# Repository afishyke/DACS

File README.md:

# DACS: Digital Automatic Changeover Switch

DACS is a discrete-logic power changeover controller that monitors grid health and switches loads between mains and inverter/battery supply. It is designed to avoid relay chatter by requiring sustained bad/good conditions before switching.

The full finite state machine (FSM), Boolean equations, and timing behavior are documented in `FSM/README.md`.

## What this project is

- A hardware-first automatic changeover system (no microcontroller in the switching core).
- A three-block architecture: sensing and conditioning, FSM decision logic, and relay output stage.
- A validated FSM implementation in both Logisim and Verilog.
- A delay-justification analysis pipeline for power-quality disturbance datasets.

## Visual overview

### 1) Full hardware architecture (KiCad)

### 2) GRID_OK comparator generation (LTspice)

### 3) Power-quality context plot

### 4) Disturbance class signal examples (delay analysis)

## Repository map

- `hardware/kicad/`: complete KiCad design (`.kicad_sch`, `.kicad_pcb`, exports).
- `grid_ok_generation/`: LTspice comparator model and generated diagram for `GRID_OK` logic.
- `simulations/logisim/`: Logisim-evolution FSM implementation.
- `simulations/verilog/`: synthesizable FSM RTL (`FSM_Grid_Stability_v2.v`).
- `simulations/ltspice/`: LTspice analog simulation files.
- `FSM/`: equation-level FSM documentation.
- `problem_statement/`: source image/script + data citation used in early framing.
- `delay_justification/`: EDA script outputs, plots, and reports for timing-delay defensibility.

## How DACS works (end-to-end)

1. **Input conditioning (Block 1):** rectifies and scales AC sense, checks voltage window and frequency window, and verifies battery level.
2. **Grid health flag generation:** combines voltage + frequency validity into a digital `GRID_OK` signal.
3. **FSM logic (Block 2):** samples `GRID_OK` on `FSM_CLK`, uses state memory + counters to enforce delay windows.
4. **Output drive (Block 3):** relay drivers route power source and shed non-essential load during backup operation.

## Core timing and threshold numbers

- FSM clock is approximately 5 Hz (report uses 5 Hz for verification, i.e. 200 ms/cycle).
- Fault confirmation window: 3 cycles (`~600 ms` at 5 Hz).
- Recovery confirmation window: 5 cycles (`~1.0 s` at 5 Hz).
- Voltage monitor window used in the design documentation is approximately:
  - upper threshold: `~4.08 V`
  - lower threshold: `~2.78 V`

Clock equation used in design notes:

$$
f = \frac{1.44}{(R_a + 2R_b)C}
$$

With `R_a = 1k\Omega`, `R_b = 150k\Omega`, `C = 1\mu F`:

$$
f \approx 4.8\,\text{Hz}, \quad T = \frac{1}{f} \approx 0.21\,\text{s}
$$

## FSM states (high level)

| State | Bits | Meaning |
| --- | --- | --- |
| ST00 | `00` | Grid mode (normal operation) |
| ST01 | `01` | Grid fault detected, waiting for confirmation |
| ST10 | `10` | Backup mode (grid confirmed bad) |
| ST11 | `11` | Grid returned, waiting for stability confirmation |

Transition intent:

- `ST00 -> ST01`: grid falls.
- `ST01 -> ST10`: fault persists until fault timer expires.
- `ST10 -> ST11`: grid returns.
- `ST11 -> ST00`: grid remains healthy until stability timer done.
- Fast rollback paths protect against short disturbances (`ST01 -> ST00`, `ST11 -> ST10`).

For the complete Boolean equations (`GRID_FALL`, `TIMER_05`, `STABILITY_DONE`, `D0`, `D1`, all term-level equations), see `FSM/README.md`.

## Verification artifacts

From the FSM verification campaign artifacts in this repository:

- 2779 automated checks reported, 0 mismatches.
- State occupancy observed:
  - ST00: 169 cycles (42.5%)
  - ST01: 96 cycles (24.1%)
  - ST10: 79 cycles (19.9%)
  - ST11: 54 cycles (13.6%)

Detailed state equations and transition logic are documented in `FSM/README.md`.

## Delay-justification EDA (dataset side)

The `delay_justification/` folder contains a full analysis pipeline for disturbance classes (17 classes, one-cycle signals at 5 kHz sampling). It supports the claim that non-zero observation windows are required before robust disturbance discrimination.

Useful plots include:

- `delay_justification/eda_outputs/plots/representative_signals_per_class.png`
- `delay_justification/eda_outputs/plots/overlay_transient_related_classes.png`
- `delay_justification/eda_outputs/plots/scatter_transient_vs_sagswell_derivative_vs_spectralspread.png`

## Main source files

- Verilog FSM: `simulations/verilog/FSM_Grid_Stability_v2.v`
- Logisim FSM: `simulations/logisim/FSM_Grid_Stabilityiteration_FINAL112233.XML (1).circ`
- Comparator LTspice: `grid_ok_generation/comparator_grid_ok.asc`
- Hardware schematic source: `hardware/kicad/schematic.kicad_sch`

## References and citations

- FSM implementation references: `simulations/verilog/FSM_Grid_Stability_v2.v`, `simulations/logisim/FSM_Grid_Stabilityiteration_FINAL112233.XML (1).circ`
- Smart-meter citation used in problem framing: `problem_statement/citations.txt`
- Comparator SPICE model source note: `grid_ok_generation/resources.txt`

## License

MIT. See `LICENSE`.

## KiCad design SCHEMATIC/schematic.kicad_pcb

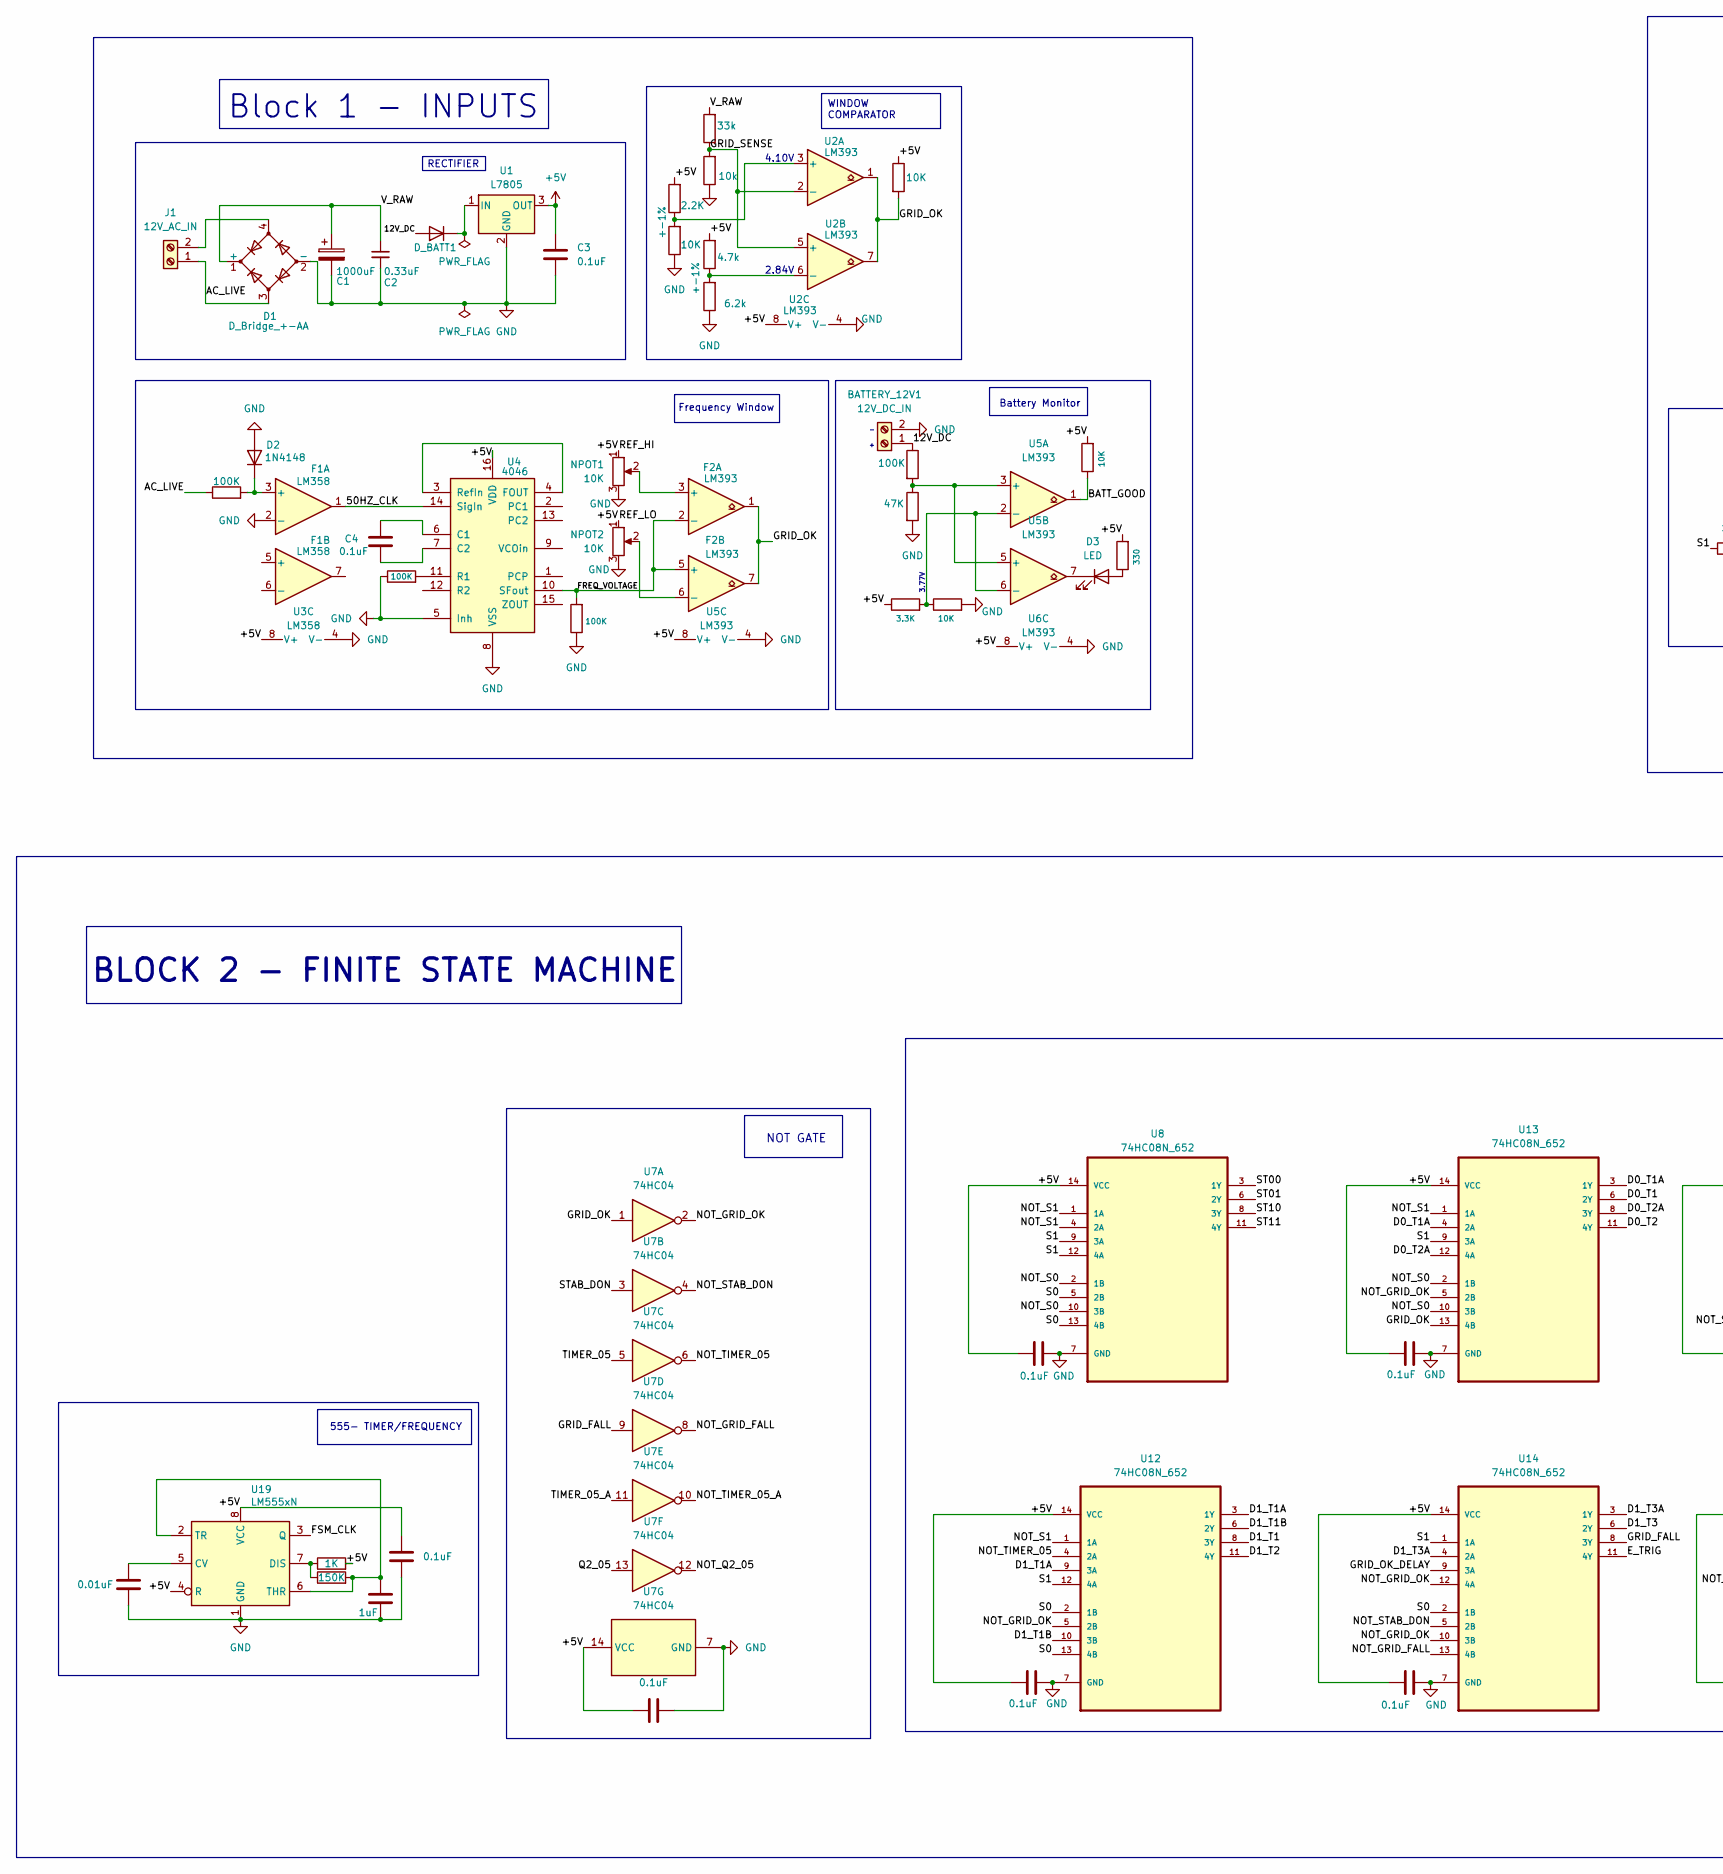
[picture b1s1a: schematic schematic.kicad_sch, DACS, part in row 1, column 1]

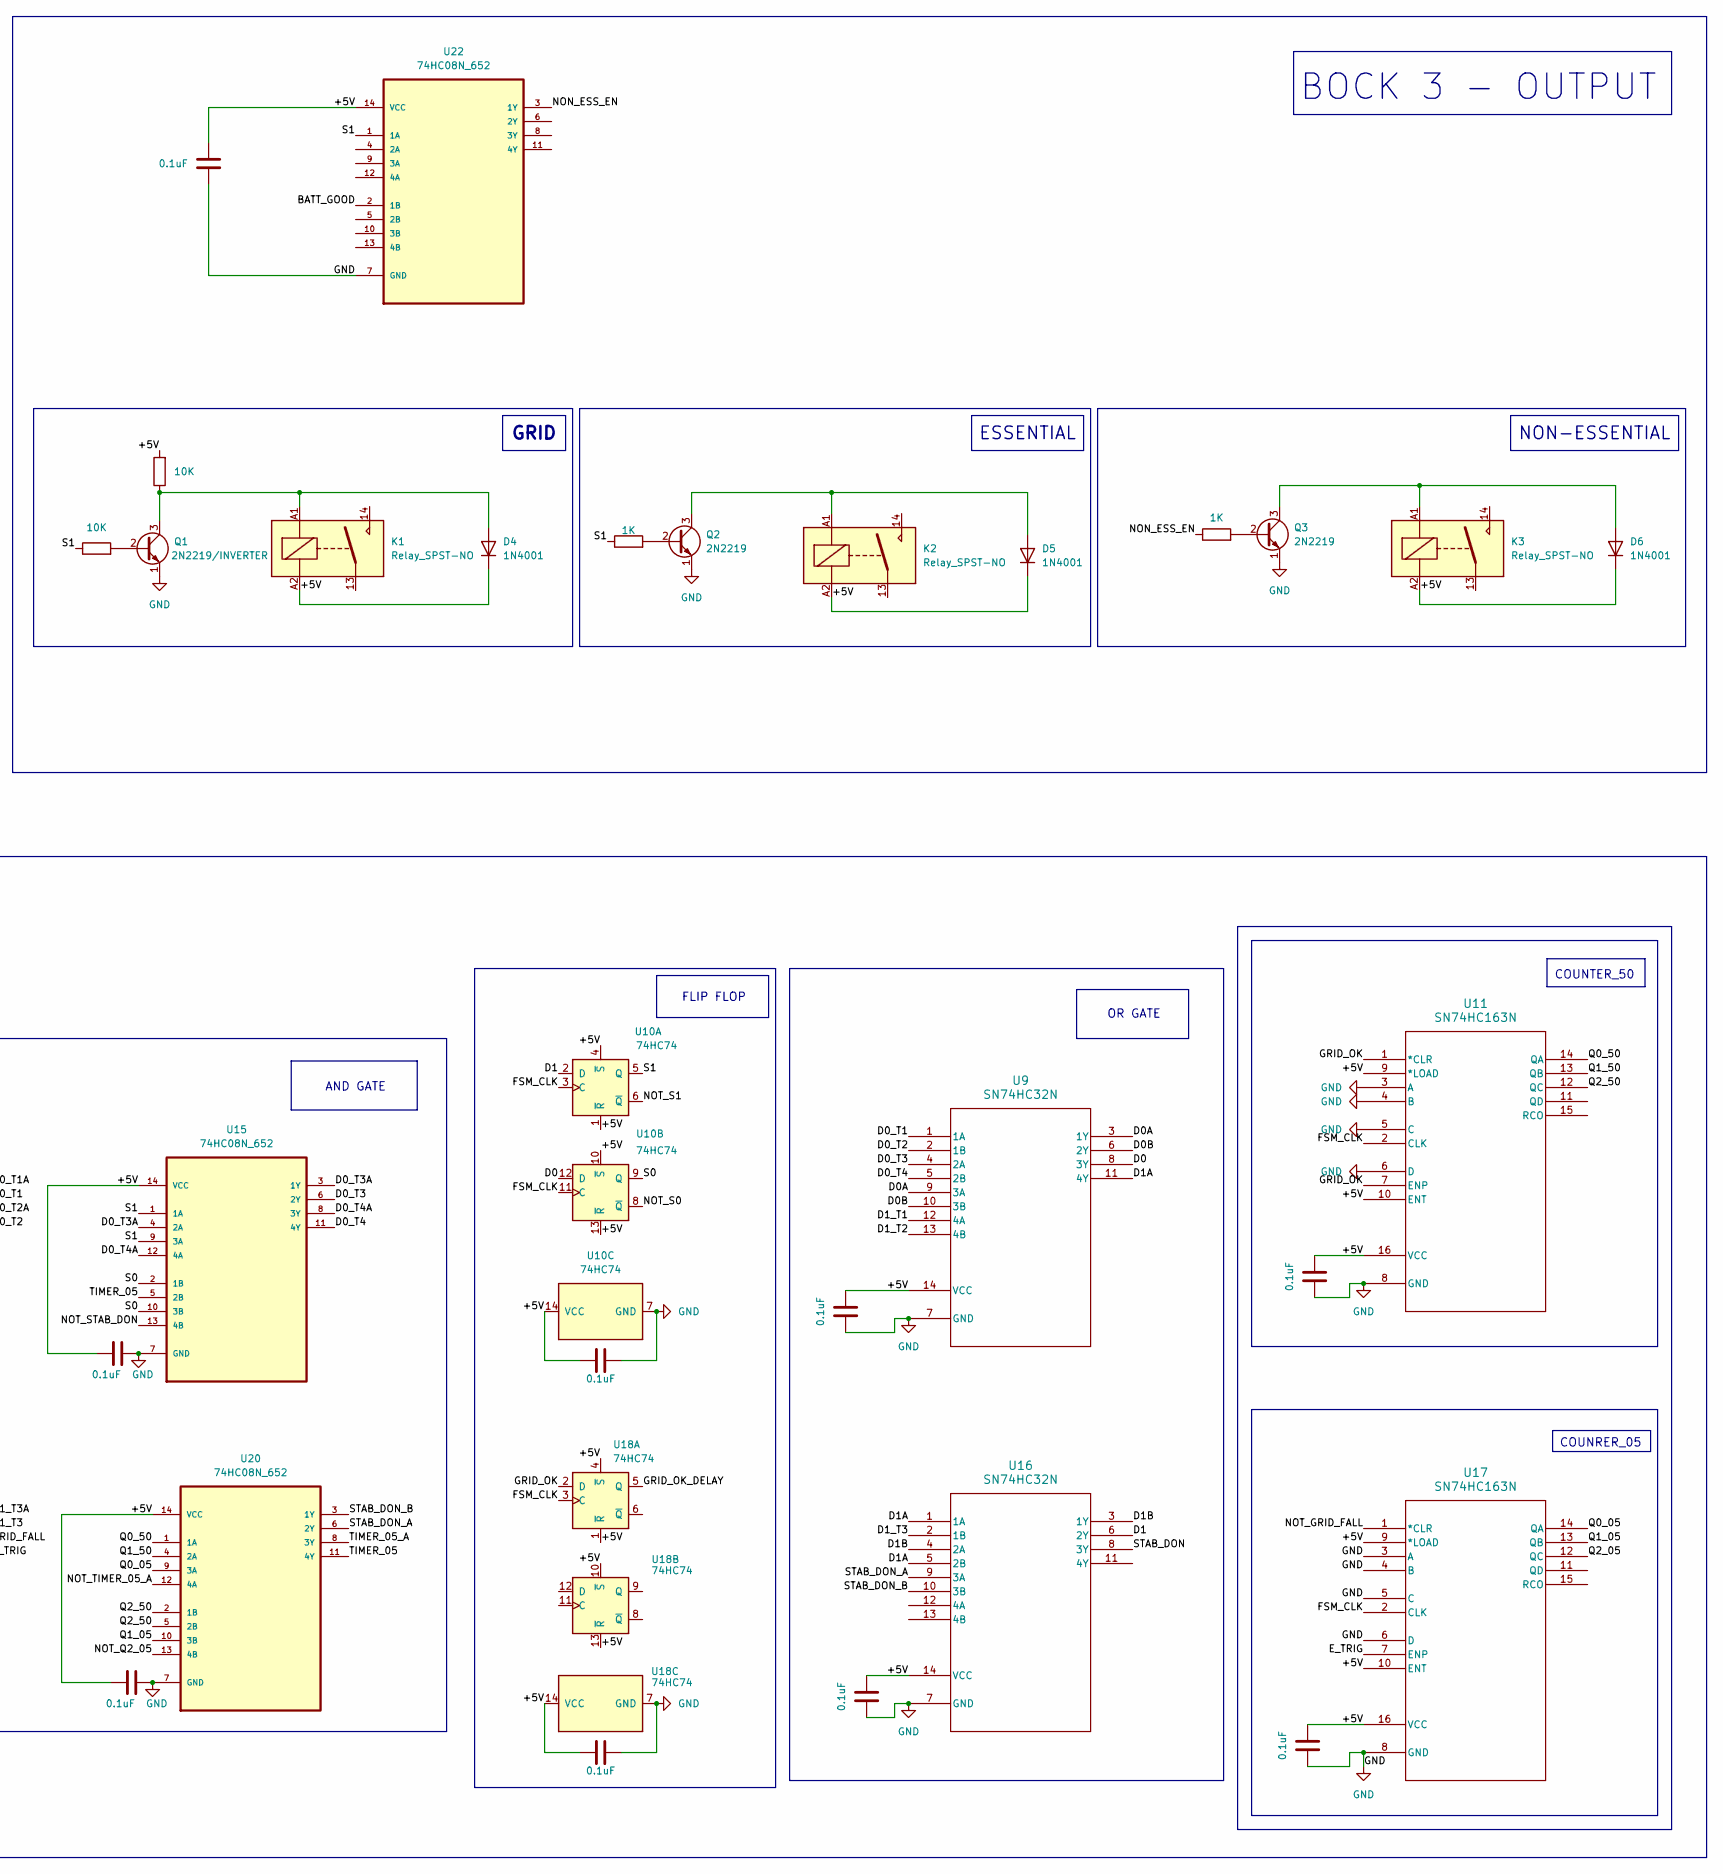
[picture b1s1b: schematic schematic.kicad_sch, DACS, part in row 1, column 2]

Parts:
10k1: 4.7k; R_Axial_DIN0207_L6.3mm_D2.5mm_P7.62mm_Horizontal
10k2: 2.2K; R_Axial_DIN0207_L6.3mm_D2.5mm_P7.62mm_Horizontal
10k3: 10K; R_Axial_DIN0207_L6.3mm_D2.5mm_P7.62mm_Horizontal
BATTERY_12V1: 12V_DC_IN; R_Axial_DIN0207_L6.3mm_D2.5mm_P7.62mm_Horizontal
C1: 1000uF; R_Axial_DIN0207_L6.3mm_D2.5mm_P7.62mm_Horizontal
C2: 0.33uF; R_Axial_DIN0207_L6.3mm_D2.5mm_P7.62mm_Horizontal
C3, C4, C5, C6, C7, C8, C9, C10, C11, C12, C13, C14, C15, C16, C17, C19, C22: 0.1uF; C_Disc_D5.0mm_W2.5mm_P2.50mm
C18: 0.01uF; C_Disc_D5.0mm_W2.5mm_P2.50mm
C20: 1uF; C_Disc_D5.0mm_W2.5mm_P2.50mm
D1: D_Bridge_+-AA; Diode_Bridge_Round_D9.8mm
D2: 1N4148; D_DO-35_SOD27_P7.62mm_Horizontal
D3: LED; LED_D5.0mm
D4, D5, D6: 1N4001; D_DO-41_SOD81_P10.16mm_Horizontal
D_BATT1: 1N4007; D_DO-41_SOD81_P10.16mm_Horizontal
F1: LM358; DIP-8_W7.62mm
F2: LM393; DIP-8_W7.62mm
J1: 12V_AC_IN; Altech_AK100_1x02_P5.00mm
K1, K2, K3: Relay_SPST-NO; Relay_SPST_Omron_G5PZ
NPOT1, NPOT2: 10K; Potentiometer_Bourns_3296W_Vertical
Q1: 2N2219/INVERTER; TO-39-3
Q2, Q3: 2N2219; TO-39-3
R1: 33k; R_Axial_DIN0207_L6.3mm_D2.5mm_P7.62mm_Horizontal
R1k1: 6.2k; R_Axial_DIN0207_L6.3mm_D2.5mm_P7.62mm_Horizontal
R2, R9, R10, R14, R15: 10K; R_Axial_DIN0207_L6.3mm_D2.5mm_P7.62mm_Horizontal
R3, R4, R5, R6: 100K; R_Axial_DIN0207_L6.3mm_D2.5mm_P7.62mm_Horizontal
R7: 47K; R_Axial_DIN0207_L6.3mm_D2.5mm_P7.62mm_Horizontal
R8: 3.3K; R_Axial_DIN0207_L6.3mm_D2.5mm_P7.62mm_Horizontal
R11: 330; R_Axial_DIN0207_L6.3mm_D2.5mm_P7.62mm_Horizontal
R12, R16, R17: 1K; R_Axial_DIN0207_L6.3mm_D2.5mm_P7.62mm_Horizontal
R13: 150K; R_Axial_DIN0207_L6.3mm_D2.5mm_P7.62mm_Horizontal
R18: 10k; R_Axial_DIN0207_L6.3mm_D2.5mm_P7.62mm_Horizontal
U1: L7805; TO-220-3_Vertical
U2, U5, U6: LM393; DIP-8_W7.62mm
U3: LM358; DIP-8_W7.62mm
U4: 4046; DIP-16_W7.62mm
U7: 74HC04; DIP-14_W7.62mm
U8, U12, U13, U14, U15, U20, U22: 74HC08N_652; DIP-14_W7.62mm; MPN 74HC08N,652
U9, U16: SN74HC32N; DIP-14_W7.62mm
U10, U18: 74HC74; DIP-14_W7.62mm
U11, U17: SN74HC163N; DIP-16_W7.62mm
U19: LM555xN; DIP-8_W7.62mm

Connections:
+5V: 10k1.2, 10k2.2, C3.1, C5.1, C6.1, C7.1, C8.1, C9.1, C10.1, C11.1, C12.1, C13.1, C14.1, C15.1, C16.1, C17.2, C19.1, C22.1, D4.1 (K), D5.1 (K), D6.1 (K), K1.A2, K2.A2, K3.A2, NPOT1.1, NPOT2.1, R2.1, R8.1, R10.2, R11.2, R12.2, R15.2, U1.3 (OUT), U2.8 (V+), U3.8 (V+), U4.16 (VDD), U5.8 (V+), U6.8 (V+), U7.14 (VCC), U8.14 (VCC), U9.14 (VCC), U10.1 (~R), U10.4 (~S), U10.10 (~S), U10.13 (~R), U10.14 (VCC), U11.9 (*LOAD), U11.10 (ENT), U11.16 (VCC), U12.14 (VCC), U13.14 (VCC), U14.14 (VCC), U15.14 (VCC), U16.14 (VCC), U17.9 (*LOAD), U17.10 (ENT), U17.16 (VCC), U18.1 (~R), U18.4 (~S), U18.10 (~S), U18.13 (~R), U18.14 (VCC), U19.4 (R), U19.8 (VCC), U20.14 (VCC), U22.14 (VCC)
/12V_DC: BATTERY_12V1.1, D_BATT1.2 (A), R6.1
/50HZ_CLK: F1.1, U4.14 (SigIn)
/AC_LIVE: D1.3, J1.1, R3.1
/BATT_GOOD: R10.1, U5.1, U22.2 (1B)
/D0: U9.8 (3Y), U10.12 (D)
/D0A: U9.3 (1Y), U9.9 (3A)
/D0B: U9.6 (2Y), U9.10 (3B)
/D0_T1: U9.1 (1A), U13.6 (2Y)
/D0_T1A: U13.3 (1Y), U13.4 (2A)
/D0_T2: U9.2 (1B), U13.11 (4Y)
/D0_T2A: U13.8 (3Y), U13.12 (4A)
/D0_T3: U9.4 (2A), U15.6 (2Y)
/D0_T3A: U15.3 (1Y), U15.4 (2A)
/D0_T4: U9.5 (2B), U15.11 (4Y)
/D0_T4A: U15.8 (3Y), U15.12 (4A)
/D1: U10.2 (D), U16.6 (2Y)
/D1A: U9.11 (4Y), U16.1 (1A), U16.5 (2B)
/D1B: U16.3 (1Y), U16.4 (2A)
/D1_T1: U9.12 (4A), U12.8 (3Y)
/D1_T1A: U12.3 (1Y), U12.9 (3A)
/D1_T1B: U12.6 (2Y), U12.10 (3B)
/D1_T2: U9.13 (4B), U12.11 (4Y)
/D1_T3: U14.6 (2Y), U16.2 (1B)
/D1_T3A: U14.3 (1Y), U14.4 (2A)
/E_TRIG: U14.11 (4Y), U17.7 (ENP)
/FREQ_VOLTAGE: F2.2 (-), F2.5 (+), R5.2, U4.10 (SFout)
/FSM_CLK: U10.3 (C), U10.11 (C), U11.2 (CLK), U17.2 (CLK), U18.3 (C), U19.3 (Q)
/GRID_FALL: U7.9, U14.8 (3Y)
/GRID_OK: F2.1, F2.7, R2.2, U2.1, U2.7, U7.1, U11.1 (*CLR), U11.7 (ENP), U13.13 (4B), U18.2 (D)
/GRID_OK_DELAY: U14.9 (3A), U18.5 (Q)
/GRID_SENSE: R1.1, R18.2, U2.2 (-), U2.5 (+)
/NON_ESS_EN: R17.1, U22.3 (1Y)
/NOT_GRID_FALL: U7.8, U14.13 (4B), U17.1 (*CLR)
/NOT_GRID_OK: U7.2, U12.5 (2B), U13.5 (2B), U14.10 (3B), U14.12 (4A)
/NOT_Q2_05: U7.12, U20.13 (4B)
/NOT_S0: U8.2 (1B), U8.10 (3B), U10.8 (~Q), U13.2 (1B), U13.10 (3B)
/NOT_S1: U8.1 (1A), U8.4 (2A), U10.6 (~Q), U12.1 (1A), U13.1 (1A)
/NOT_STAB_DON: U7.4, U14.5 (2B), U15.13 (4B)
/NOT_TIMER_05: U7.6, U12.4 (2A)
/NOT_TIMER_05_A: U7.10, U20.12 (4A)
/Q0_05: U17.14 (QA), U20.9 (3A)
/Q0_50: U11.14 (QA), U20.1 (1A)
/Q1_05: U17.13 (QB), U20.10 (3B)
/Q1_50: U11.13 (QB), U20.4 (2A)
/Q2_05: U7.13, U17.12 (QC)
/Q2_50: U11.12 (QC), U20.2 (1B), U20.5 (2B)
/S0: U8.5 (2B), U8.13 (4B), U10.9 (Q), U12.2 (1B), U12.13 (4B), U14.2 (1B), U15.2 (1B), U15.10 (3B)
/S1: R14.1, R16.1, U8.9 (3A), U8.12 (4A), U10.5 (Q), U12.12 (4A), U13.9 (3A), U14.1 (1A), U15.1 (1A), U15.9 (3A), U22.1 (1A)
/ST00: U8.3 (1Y)
/ST01: U8.6 (2Y)
/ST10: U8.8 (3Y)
/ST11: U8.11 (4Y)
/STAB_DON: U7.3, U16.8 (3Y)
/STAB_DON_A: U16.9 (3A), U20.6 (2Y)
/STAB_DON_B: U16.10 (3B), U20.3 (1Y)
/TIMER_05: U7.5, U15.5 (2B), U20.11 (4Y)
/TIMER_05_A: U7.11, U20.8 (3Y)
/V_RAW: C1.1, C2.1, D1.1 (+), R1.2; also elsewhere on the board
GND: 10k3.1, BATTERY_12V1.2, C1.2, C2.2, C3.2, C5.2, C6.2, C7.2, C8.2, C9.2, C10.2, C11.2, C12.2, C13.2, C14.2, C15.2, C16.2, C17.1, C18.1, C19.2, C20.1, C22.2, D1.2 (-), D2.2 (A), F1.2 (-), NPOT1.3, NPOT2.3, Q1.1 (E), Q2.1 (E), Q3.1 (E), R1k1.1, R4.1, R5.1, R7.2, R9.2, R18.1, U1.2 (GND), U2.4 (V-), U3.4 (V-), U4.5 (Inh), U4.8 (VSS), U5.4 (V-), U6.4 (V-), U7.7 (GND), U8.7 (GND), U9.7 (GND), U10.7 (GND), U11.3 (A), U11.4 (B), U11.5 (C), U11.6 (D), U11.8 (GND), U12.7 (GND), U13.7 (GND), U14.7 (GND), U15.7 (GND), U16.7 (GND), U17.3 (A), U17.4 (B), U17.5 (C), U17.6 (D), U17.8 (GND), U18.7 (GND), U19.1 (GND), U20.7 (GND), U22.7 (GND)
unnamed: D2.1 (K), F1.3 (+), R3.2
unnamed: D3.2 (A), R11.1
unnamed: D3.1 (K), U5.7
unnamed: D4.2 (A), K1.A1, Q1.3 (C), R15.1
unnamed: D5.2 (A), K2.A1, Q2.3 (C)
unnamed: D6.2 (A), K3.A1, Q3.3 (C)
unnamed 66: D_BATT1.1 (K), U1.1 (IN); also elsewhere on the board
unnamed: F2.3 (+), NPOT1.2
unnamed: F2.6 (-), NPOT2.2
unnamed: D1.4, J1.2
unnamed: Q1.2 (B), R14.2
unnamed: Q2.2 (B), R16.2
unnamed: Q3.2 (B), R17.2
unnamed: 10k2.1, 10k3.2, U2.3 (+)
unnamed: 10k1.1, R1k1.2, U2.6 (-)
unnamed: C4.1, U4.6 (C1)
unnamed: C4.2, U4.7 (C2)
unnamed: U4.3 (RefIn), U4.4 (FOUT)
unnamed: R4.2, U4.11 (R1)
unnamed: R6.2, R7.1, U5.3 (+), U5.5 (+)
unnamed: R8.2, R9.1, U5.2 (-), U5.6 (-)
unnamed: C18.2, U19.5 (CV)
unnamed: R12.1, R13.1, U19.7 (DIS)
unnamed: C20.2, R13.2, U19.2 (TR), U19.6 (THR)

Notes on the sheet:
NON-ESSENTIAL
COUNRER_05
WINDOW COMPARATOR
ESSENTIAL
GRID
AND GATE
Block 1 - INPUTS
COUNTER_50
BOCK 3 - OUTPUT
4.10V
BLOCK 2 - FINITE STATE MACHINE
3.77V
555- TIMER/FREQUENCY
2.84V
Frequency Window
NOT GATE
RECTIFIER
FLIP FLOP
Battery Monitor
OR GATE

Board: 2 copper layers, 84 parts (0 on the bottom side), 80 nets, no tracks yet.

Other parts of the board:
D_GRID1: 1N4007; D_DO-41_SOD81_P10.16mm_Horizontal

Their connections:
/V_RAW: D_GRID1.2 (A); also elsewhere on the board
unnamed 66: D_GRID1.1 (K); also elsewhere on the board

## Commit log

2026-01-03 Initial commit: Project structure and documentation
2026-01-03 added README
2026-01-03 Fix math rendering in README for GitHub compatibility
2026-01-03 Add files via upload
    Fixed errors in schematic
2026-04-10 Refine README and add markdown FSM documentation
2026-04-10 Reorganize project files and add supporting assets
